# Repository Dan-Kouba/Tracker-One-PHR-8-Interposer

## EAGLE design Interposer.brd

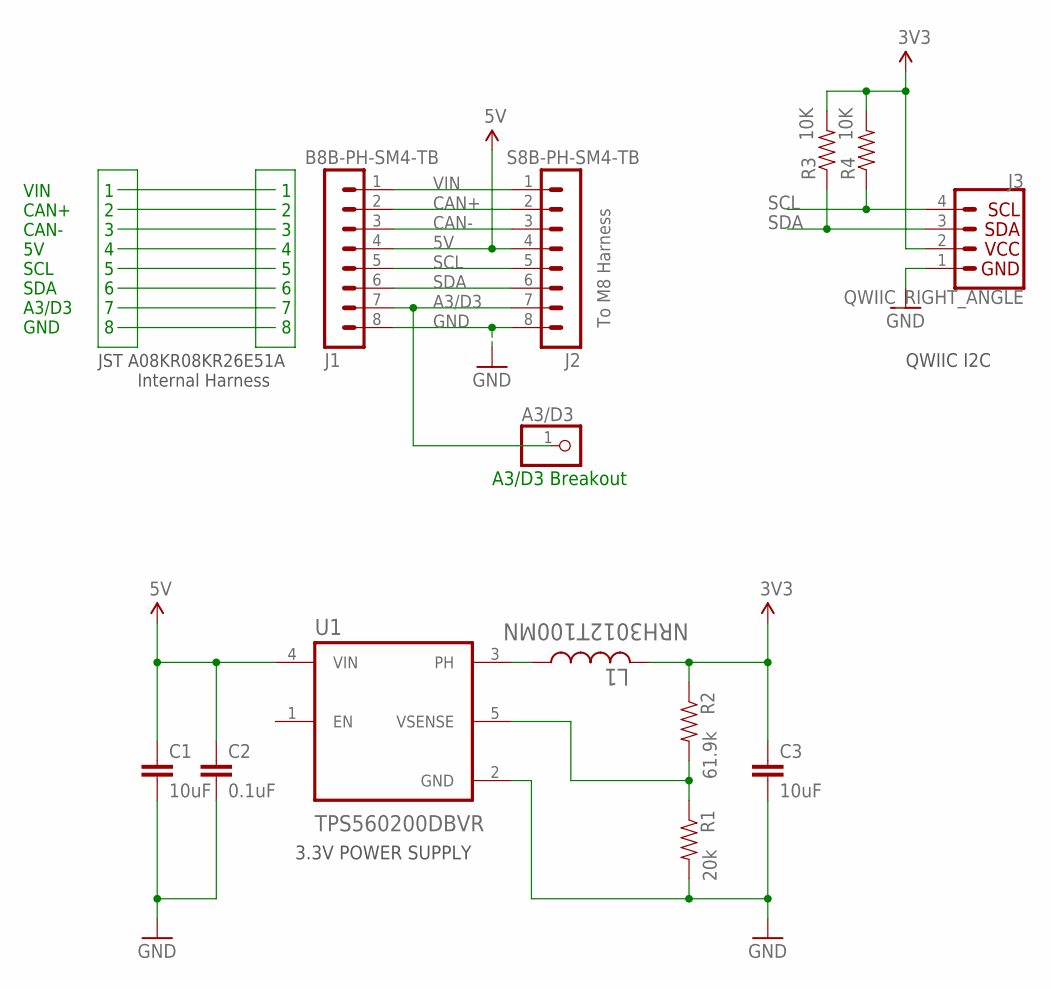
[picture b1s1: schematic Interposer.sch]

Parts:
A3/D3: PINHD-1X1; 1X01
C1, C3: 10uF; 0603-CAP
C2: 0.1uF; 0603-CAP
J1: B8B-PH-SM4-TB
J2: S8B-PH-SM4-TB
J3: QWIIC_RIGHT_ANGLE; JST04_1MM_RA
L1: NRH3012T100MN; IND_TAIYO_NRH3012_TAY
R1: 20k; 0603-RES
R2: 61.9k; 0603-RES
R3, R4: 10K; 0603-RES
U1: TPS560200DBVR; SOT95P280X145-5N

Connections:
3V3: C3.1, J3.2, L1.2, R2.1, R3.2, R4.2
3V3_SENSE: R1.1, R2.2, U1.5 (VSENSE)
3V3_SW: L1.1, U1.3 (PH)
5V: C1.1, C2.1, J1.4, J2.4, U1.4 (VIN)
A3/D3: A3/D3.1, J1.7, J2.7
CAN+: J1.2, J2.2
CAN-: J1.3, J2.3
GND: C1.2, C2.2, C3.2, J1.8, J2.8, J3.1, R1.2, U1.2 (GND)
SCL: J1.5, J2.5, J3.4, R4.1
SDA: J1.6, J2.6, J3.3, R3.1
VIN: J1.1, J2.1

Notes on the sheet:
3.3V POWER SUPPLY
QWIIC I2C
A3/D3 Breakout
VIN CAN+ CAN- 5V SCL SDA A3/D3 GND
1 2 3 4 5 6 7 8
JST A08KR08KR26E51A
Internal Harness
To M8 Harness

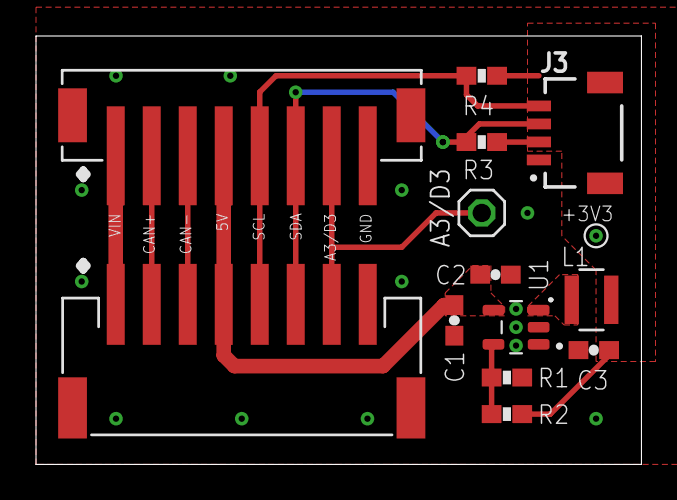
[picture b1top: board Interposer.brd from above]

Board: 2 copper layers, 33.6 x 23.8 mm, 13 parts (0 on the bottom side), 11 nets.

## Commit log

2020-09-08 Add interposer V2 board files
2020-09-08 Add simple code example with the Sparkfun RFID starter kit
2020-09-08 Move example code into it's own folder
2020-09-16 Remove some code leftovers from an old project
